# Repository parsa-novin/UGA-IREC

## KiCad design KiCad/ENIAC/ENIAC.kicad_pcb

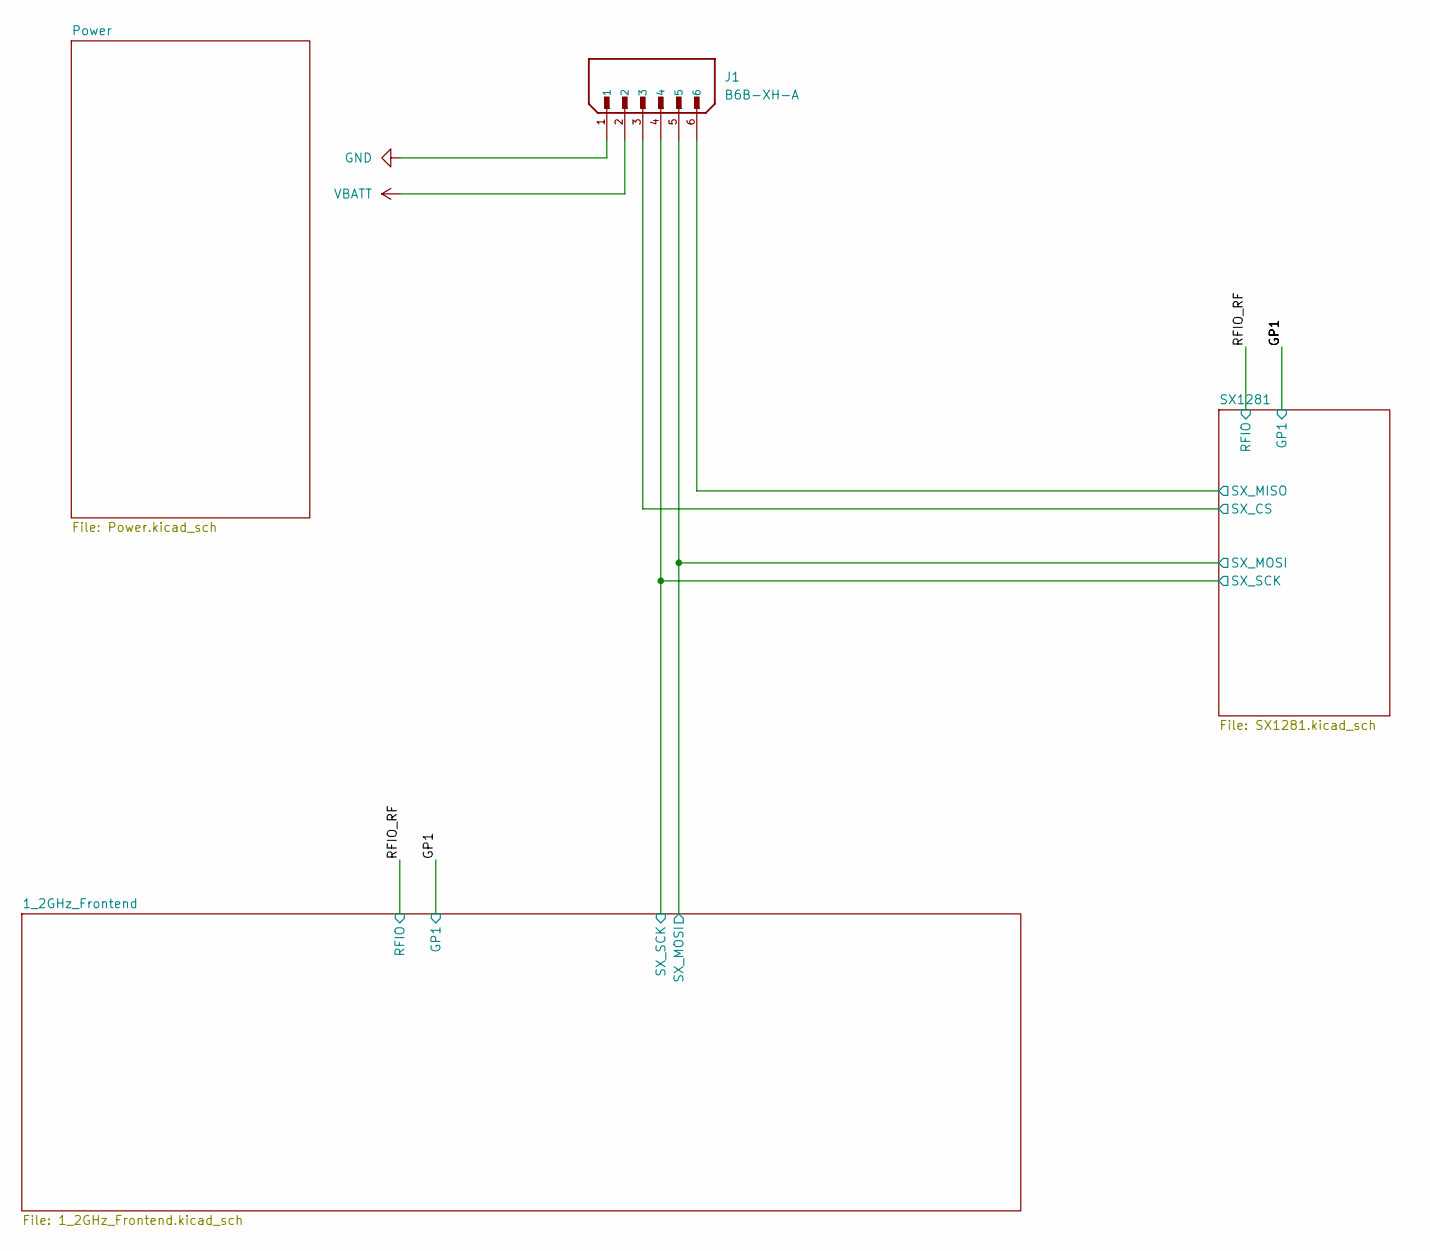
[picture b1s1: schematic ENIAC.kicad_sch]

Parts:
J1: B6B-XH-A; JST_EH_S6B-EH_1x06_P2.50mm_Horizontal; PARTREV 7/4/21

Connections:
/1_2GHz_Frontend/SX_MOSI: J1.5; also elsewhere on the board
/1_2GHz_Frontend/SX_SCK: J1.4; also elsewhere on the board
/SX1281/SX_CS: J1.3; also elsewhere on the board
/SX1281/SX_MISO: J1.6; also elsewhere on the board
VBATT: J1.2; also elsewhere on the board

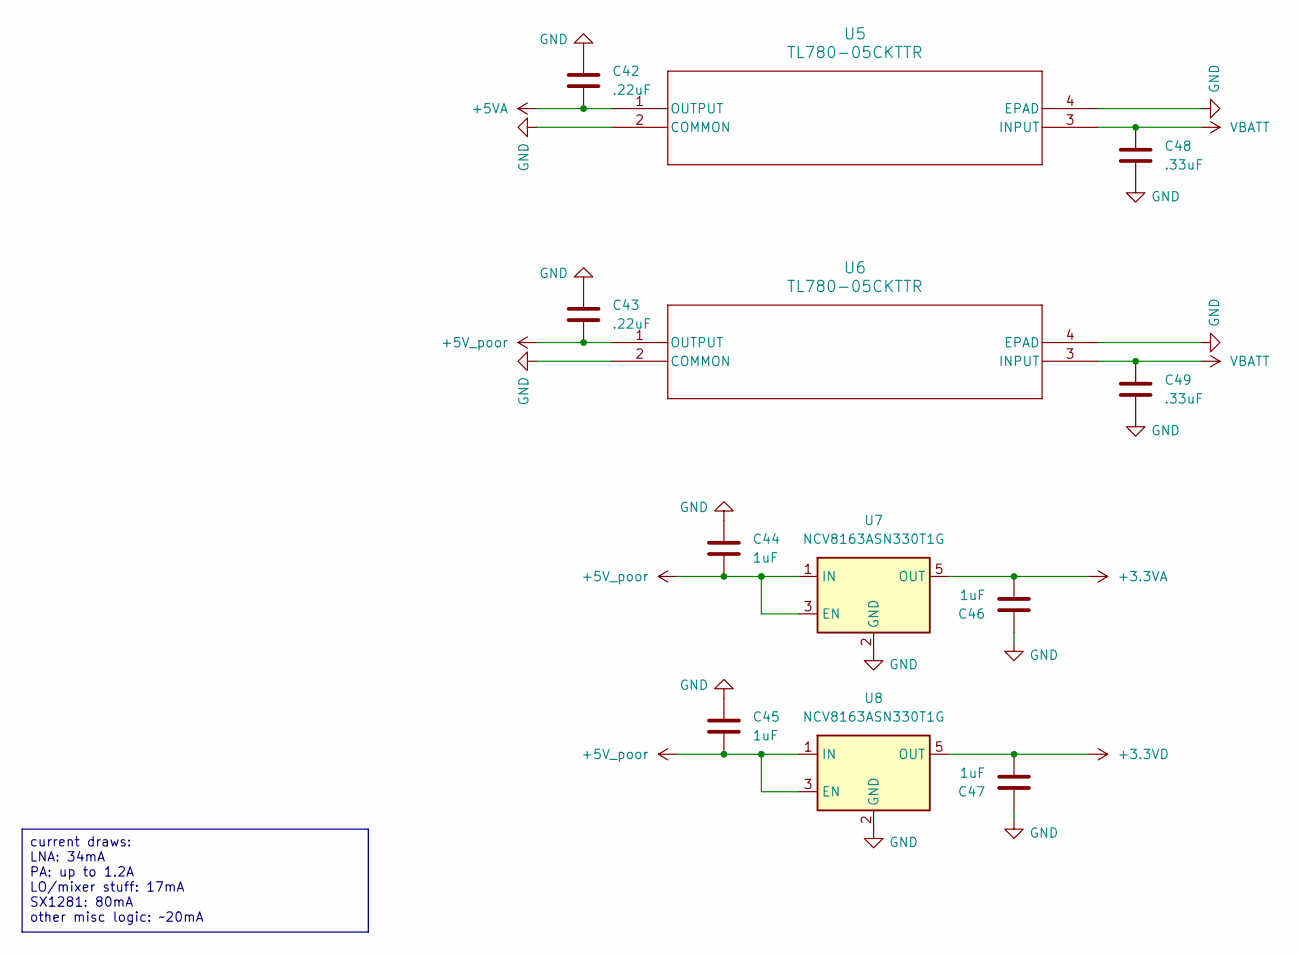
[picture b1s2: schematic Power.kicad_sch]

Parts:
C42, C43: .22uF; C_0603_1608Metric
C44, C45, C46, C47: 1uF; C_0603_1608Metric
C48, C49: .33uF; C_0603_1608Metric
U5, U6: TL780-05CKTTR; TO-263-3_TabPin4
U7, U8: NCV8163ASN330T1G; TSOT-23-5

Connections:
+3.3VA: C46.2, U7.5 (OUT); also elsewhere on the board
+3.3VD: C47.2, U8.5 (OUT); also elsewhere on the board
+5VA: C42.2, U5.1 (OUTPUT); also elsewhere on the board
+5V_poor: C43.2, C44.2, C45.2, U6.1 (OUTPUT), U7.1 (IN), U7.3 (EN), U8.1 (IN), U8.3 (EN)
VBATT: C48.1, C49.1, U5.3 (INPUT), U6.3 (INPUT); also elsewhere on the board

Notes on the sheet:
current draws: LNA: 34mA PA: up to 1.2A LO/mixer stuff: 17mA SX1281: 80mA other misc logic: ~20mA

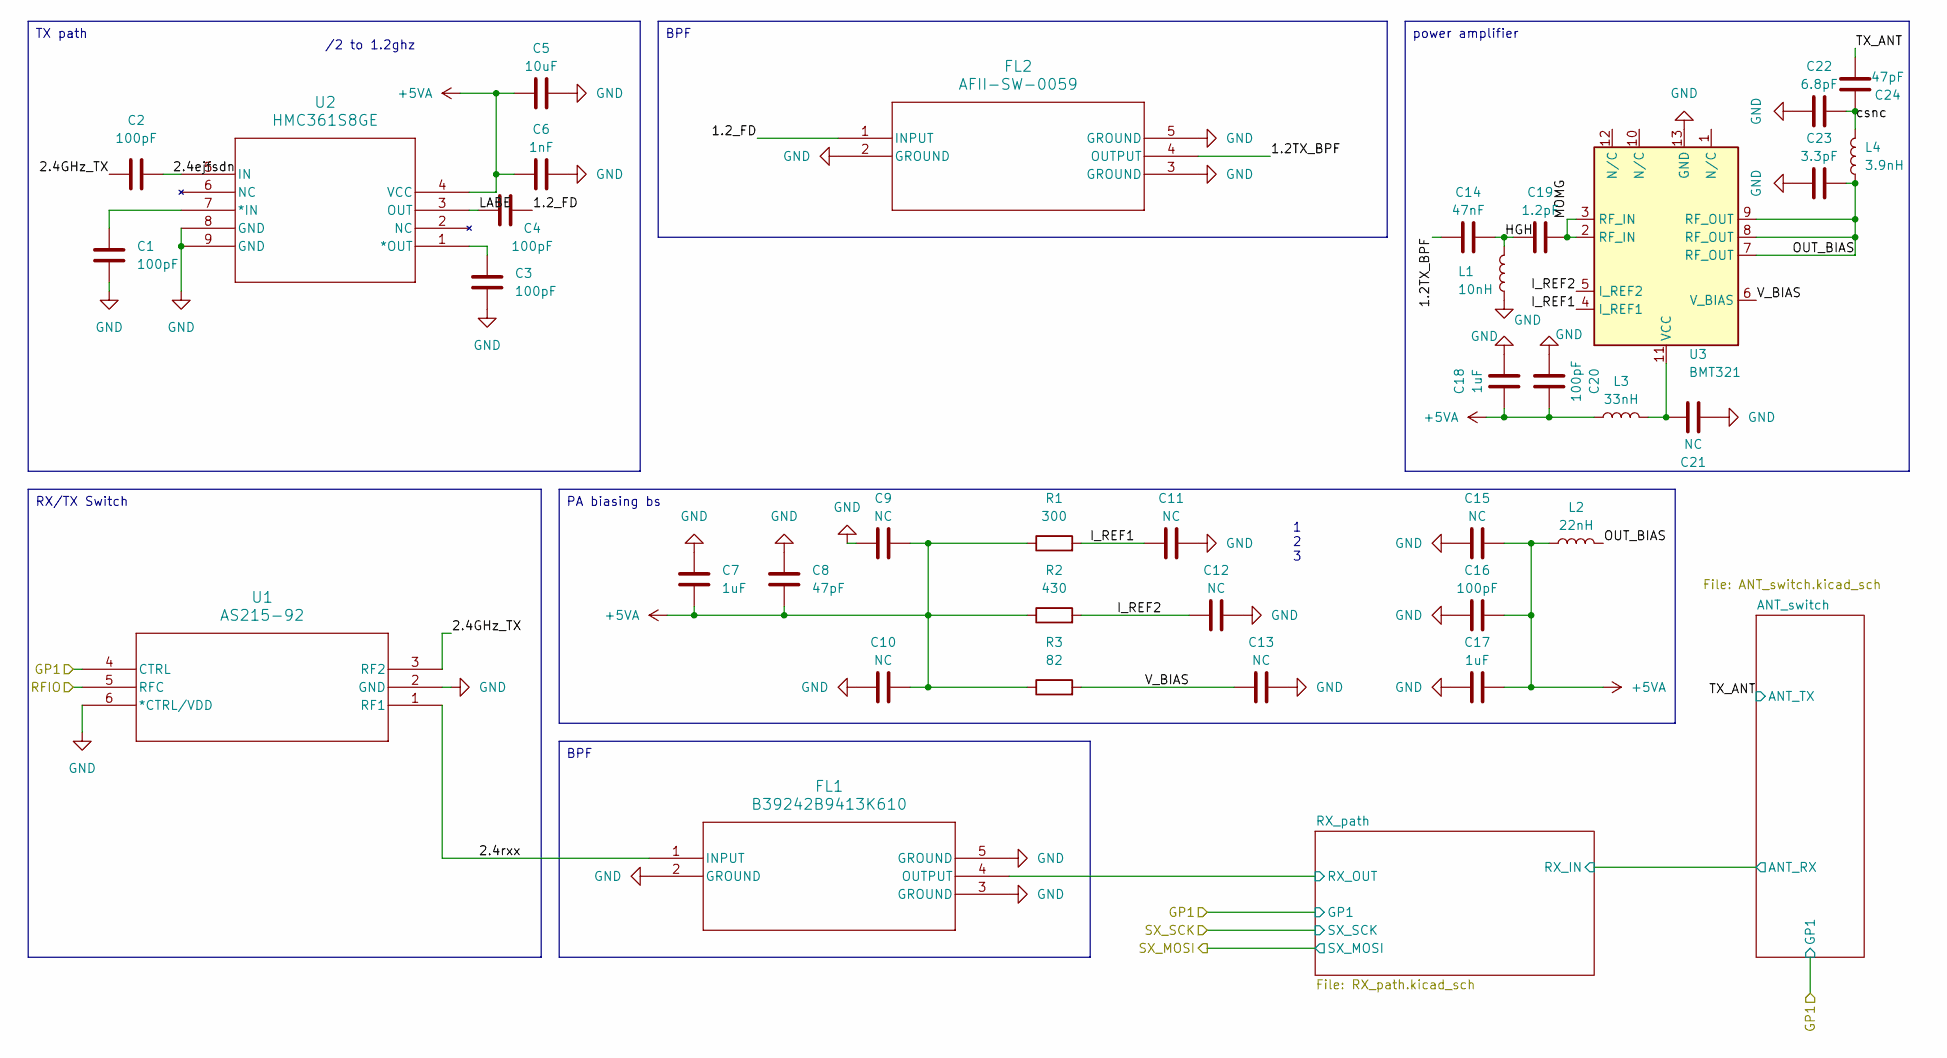
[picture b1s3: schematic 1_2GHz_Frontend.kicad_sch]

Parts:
C1, C2, C3, C4, C16, C20: 100pF; C_0603_1608Metric
C5: 10uF; C_0603_1608Metric
C6: 1nF; C_0603_1608Metric
C7, C17, C18: 1uF; C_0603_1608Metric
C8, C24: 47pF; C_0603_1608Metric
C9, C10, C11, C12, C13, C15, C21: NC; C_0603_1608Metric
C14: 47nF; C_0603_1608Metric
C19: 1.2pF; C_0603_1608Metric
C22: 6.8pF; C_0603_1608Metric
C23: 3.3pF; C_0603_1608Metric
FL1: B39242B9413K610; FIL_AFS14A04-1575.42-T3
FL2: AFII-SW-0059; FIL_AFS14A04-1575.42-T3
L1: 10nH; L_0603_1608Metric
L2: 22nH; L_0603_1608Metric
L3: 33nH; L_0603_1608Metric
L4: 3.9nH; L_0603_1608Metric
R1: 300; R_0603_1608Metric
R2: 430; R_0603_1608Metric
R3: 82; R_0603_1608Metric
U1: AS215-92; SOT-363_SC-70-6_Handsoldering
U2: HMC361S8GE; SOIC-8-1EP_3.9x4.9mm_P1.27mm_EP2.41x3.3mm_ThermalVias
U3: BMT321; VQFN-12-1EP_4x4mm_P0.8mm_EP2.1x2.1mm_ThermalVias

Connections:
+5VA: C5.1, C6.1, C7.2, C8.2, C9.1, C10.2, C15.2, C16.2, C17.2, C18.1, C20.2, L2.1, L3.1, R1.1, R2.1, R3.1, U2.4 (VCC); also elsewhere on the board
/1_2GHz_Frontend/1.2TX_BPF: C14.1, FL2.4 (OUTPUT)
/1_2GHz_Frontend/1.2_FD: C4.1, FL2.1 (INPUT)
/1_2GHz_Frontend/2.4GHz_TX: C2.1, U1.3 (RF2)
/1_2GHz_Frontend/2.4ejfsdn: C2.2, U2.5 (IN)
/1_2GHz_Frontend/2.4rxx: FL1.1 (INPUT), U1.1 (RF1)
/1_2GHz_Frontend/HGH: C14.2, C19.1, L1.2
/1_2GHz_Frontend/I_REF1: C11.1, R1.2, U3.4 (I_REF1)
/1_2GHz_Frontend/I_REF2: C12.1, R2.2, U3.5 (I_REF2)
/1_2GHz_Frontend/LABE: C4.2, U2.3 (OUT)
/1_2GHz_Frontend/MOMG: C19.2, U3.2 (RF_IN), U3.3 (RF_IN)
/1_2GHz_Frontend/OUT_BIAS: C23.2, L2.2, L4.1, U3.7 (RF_OUT), U3.8 (RF_OUT), U3.9 (RF_OUT)
/1_2GHz_Frontend/RX_path/RX_OUT: FL1.4 (OUTPUT); also elsewhere on the board
/1_2GHz_Frontend/TX_ANT: C24.2; also elsewhere on the board
/1_2GHz_Frontend/V_BIAS: C13.1, R3.2, U3.6 (V_BIAS)
/1_2GHz_Frontend/csnc: C22.2, C24.1, L4.2
/GP1: U1.4 (CTRL); also elsewhere on the board
/RFIO_RF: U1.5 (RFC); also elsewhere on the board
unnamed: C1.1, U2.7 (*IN)
unnamed: C3.1, U2.1 (*OUT)
unnamed: C21.2, L3.2, U3.11 (VCC)

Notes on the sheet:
1 2 3
/2 to 1.2ghz
BPF
RX/TX Switch
TX path
power amplifier
PA biasing bs

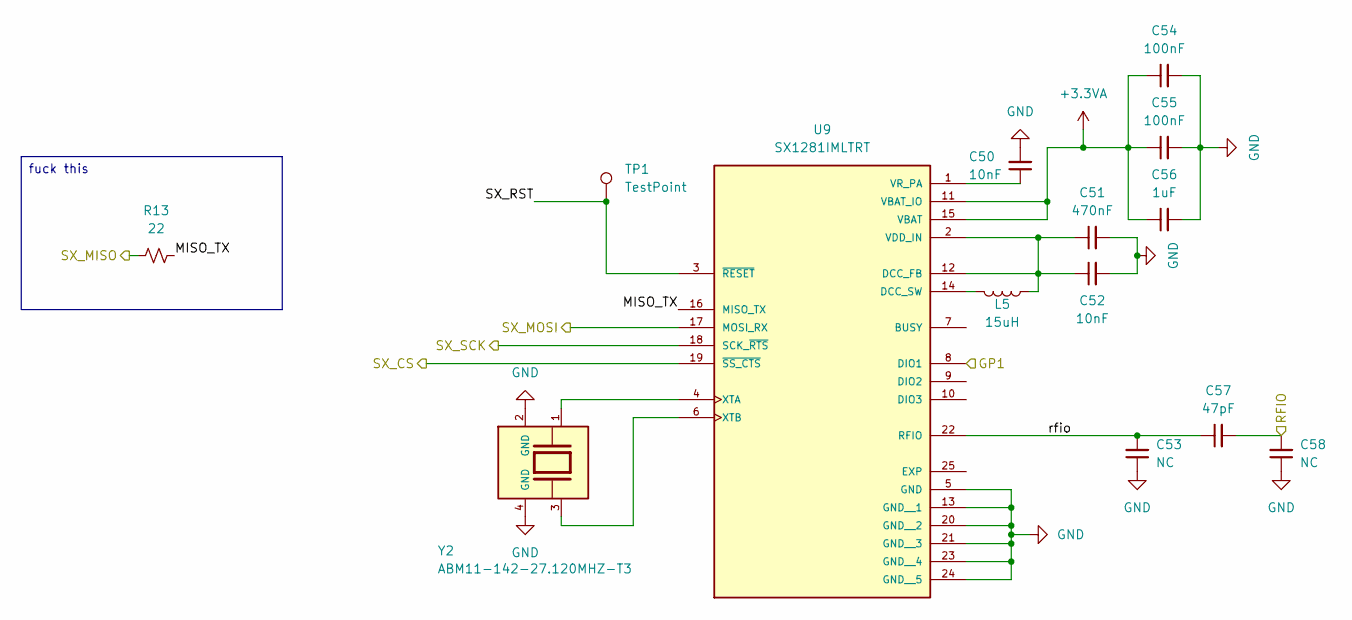
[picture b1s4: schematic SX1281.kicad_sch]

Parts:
C50, C52: 10nF; C_0603_1608Metric
C51: 470nF; C_0603_1608Metric
C53, C58: NC; C_0603_1608Metric
C54, C55: 100nF; C_0603_1608Metric
C56: 1uF; C_0603_1608Metric
C57: 47pF; C_0603_1608Metric
L5: 15uH; L_0603_1608Metric
R13: 22; R_0603_1608Metric
TP1: TestPoint
U9: SX1281IMLTRT; QFN-24-1EP_4x4mm_P0.5mm_EP2.6x2.6mm_ThermalVias; PARTREV 3.3
Y2: ABM11-142-27.120MHZ-T3; XTAL_ABM11-142-27.120MHZ-T3; PARTREV 06.19.15

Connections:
+3.3VA: C54.1, C55.1, C56.1, U9.11 (VBAT_IO), U9.15 (VBAT); also elsewhere on the board
/1_2GHz_Frontend/SX_MOSI: U9.17 (MOSI_RX); also elsewhere on the board
/1_2GHz_Frontend/SX_SCK: U9.18 (SCK_~RTS); also elsewhere on the board
/GP1: U9.8 (DIO1); also elsewhere on the board
/RFIO_RF: C57.2, C58.2; also elsewhere on the board
/SX1281/MISO_TX: R13.1, U9.16 (MISO_TX)
/SX1281/SX_CS: U9.19 (~SS_CTS); also elsewhere on the board
/SX1281/SX_MISO: R13.2; also elsewhere on the board
/SX1281/SX_RST: TP1.1, U9.3 (~RESET)
/SX1281/rfio: C53.2, C57.1, U9.22 (RFIO)
unnamed: C51.1, C52.1, L5.1, U9.2 (VDD_IN), U9.12 (DCC_FB)
unnamed: L5.2, U9.14 (DCC_SW)
unnamed: C50.1, U9.1 (VR_PA)
unnamed: U9.4 (XTA), Y2.1
unnamed: U9.6 (XTB), Y2.3

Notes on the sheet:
fuck this

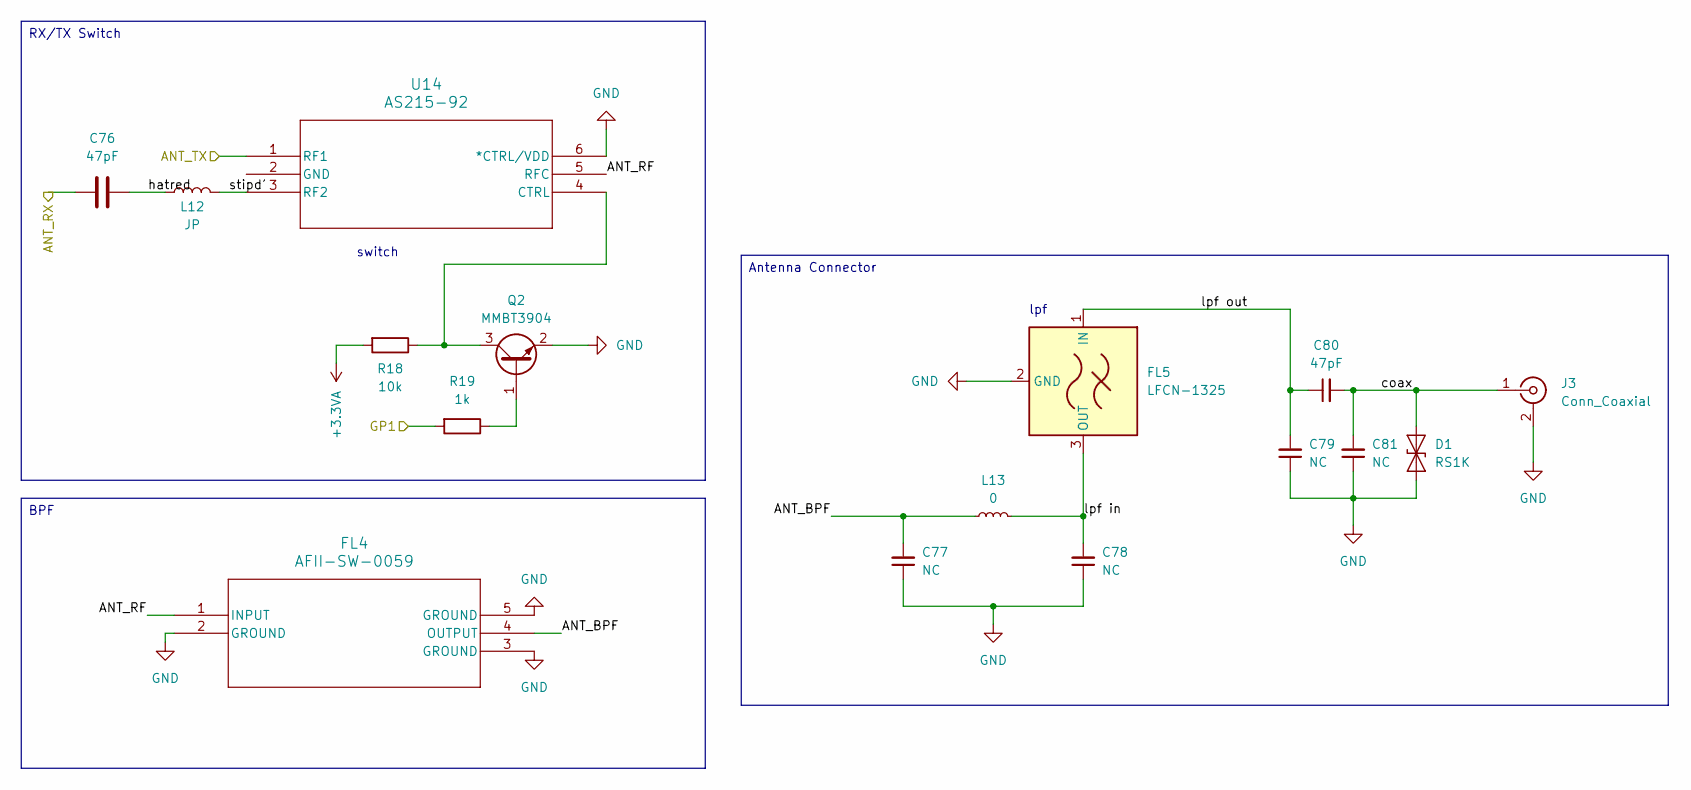
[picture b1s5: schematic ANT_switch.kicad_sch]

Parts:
C76, C80: 47pF; C_0603_1608Metric
C77, C78, C79, C81: NC; C_0603_1608Metric
D1: RS1K; D_SMA
FL4: AFII-SW-0059; FIL_AFS14A04-1575.42-T3
FL5: LFCN-1325; Filter_Mini-Circuits_FV1206
J3: Conn_Coaxial; SMA_Molex_73251-1153_EdgeMount_Horizontal
L12: JP; L_0603_1608Metric
L13: 0; L_0603_1608Metric
Q2: MMBT3904; SOT-23
R18: 10k; R_0603_1608Metric
R19: 1k; R_0603_1608Metric
U14: AS215-92; SOT-363_SC-70-6_Handsoldering

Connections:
+3.3VA: R18.2; also elsewhere on the board
/1_2GHz_Frontend/ANT_switch/ANT_BPF: C77.2, FL4.4 (OUTPUT), L13.1
/1_2GHz_Frontend/ANT_switch/ANT_RF: FL4.1 (INPUT), U14.5 (RFC)
/1_2GHz_Frontend/ANT_switch/ANT_RX: C76.1; also elsewhere on the board
/1_2GHz_Frontend/ANT_switch/coax: C80.2, C81.2, D1.2 (A2), J3.1 (In)
/1_2GHz_Frontend/ANT_switch/hatred: C76.2, L12.1
/1_2GHz_Frontend/ANT_switch/lpf in: C78.2, FL5.3 (OUT), L13.2
/1_2GHz_Frontend/ANT_switch/lpf out: C79.2, C80.1, FL5.1 (IN)
/1_2GHz_Frontend/ANT_switch/stipd': L12.2, U14.3 (RF2)
/1_2GHz_Frontend/TX_ANT: U14.1 (RF1); also elsewhere on the board
/GP1: R19.2; also elsewhere on the board
unnamed: Q2.1 (B), R19.1
unnamed: Q2.3 (C), R18.1, U14.4 (CTRL)

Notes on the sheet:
switch
lpf
Antenna Connector
RX/TX Switch
BPF

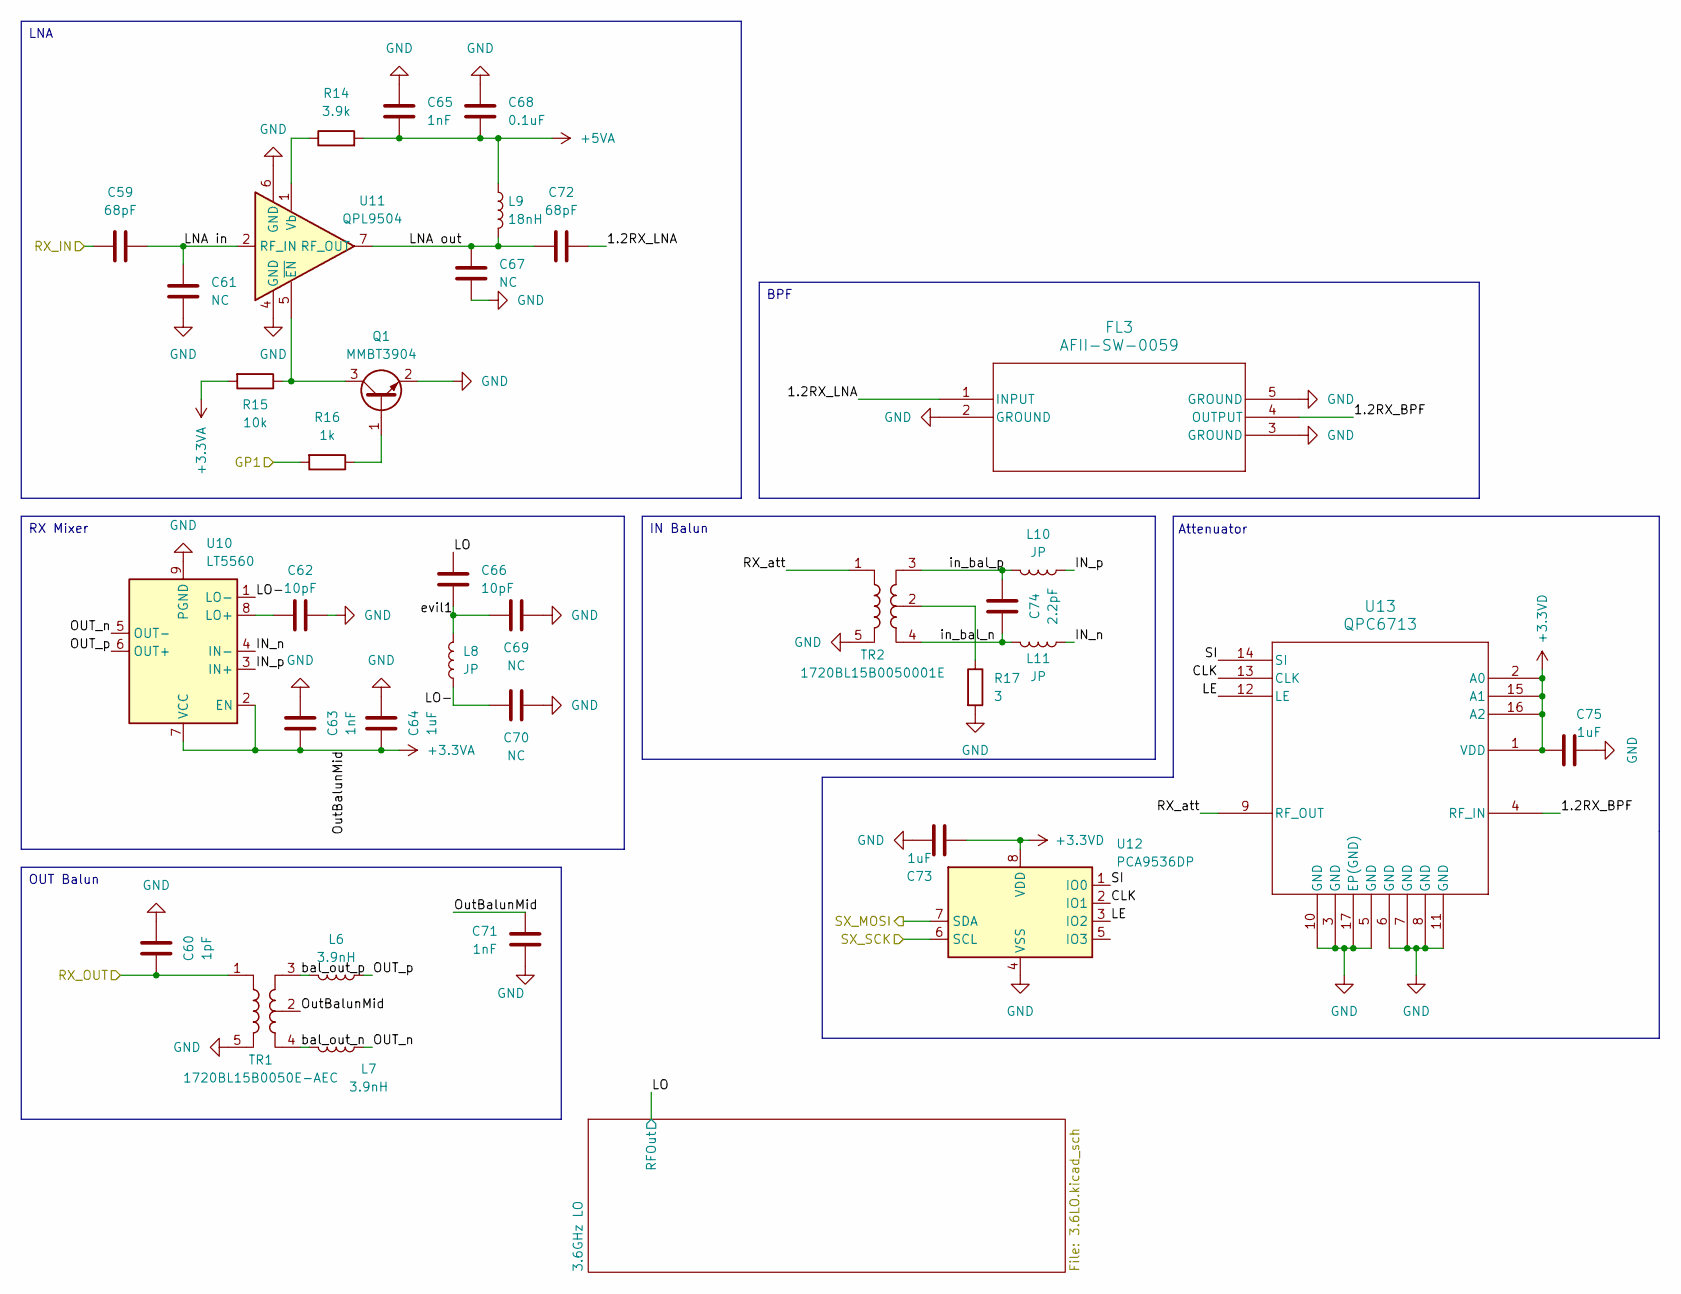
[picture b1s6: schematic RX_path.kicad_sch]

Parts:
C59, C72: 68pF; C_0603_1608Metric
C60: 1pF; C_0603_1608Metric
C61, C67, C69, C70: NC; C_0603_1608Metric
C62, C66: 10pF; C_0603_1608Metric
C63, C65, C71: 1nF; C_0603_1608Metric
C64, C73, C75: 1uF; C_0603_1608Metric
C68: 0.1uF; C_0603_1608Metric
C74: 2.2pF; C_0603_1608Metric
FL3: AFII-SW-0059; FIL_AFS14A04-1575.42-T3
L6, L7: 3.9nH; L_0603_1608Metric
L8, L10, L11: JP; L_0603_1608Metric
L9: 18nH; L_0603_1608Metric
Q1: MMBT3904; SOT-23
R14: 3.9k; R_0603_1608Metric
R15: 10k; R_0603_1608Metric
R16: 1k; R_0603_1608Metric
R17: 3; R_0603_1608Metric
TR1: 1720BL15B0050E-AEC; SMT_15B0050E_JOT
TR2: 1720BL15B0050001E; SMT_15B0050E_JOT
U10: LT5560; DFN-8-1EP_3x3mm_P0.5mm_EP1.66x2.38mm
U11: QPL9504; DFN-8-1EP_2x2mm_P0.5mm_EP0.8x1.6mm
U12: PCA9536DP; TSSOP-8_3x3mm_P0.65mm
U13: QPC6713; QFN-16-1EP_3x3mm_P0.5mm_EP1.7x1.7mm_ThermalVias

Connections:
+3.3VA: C63.1, C64.1, C71.1, R15.2, TR1.2, U10.2 (EN), U10.7 (VCC); also elsewhere on the board
+3.3VD: C73.1, C75.1, U12.8 (VDD), U13.1 (VDD), U13.2 (A0), U13.15 (A1), U13.16 (A2); also elsewhere on the board
+5VA: C65.2, C68.2, L9.1, R14.2; also elsewhere on the board
/1_2GHz_Frontend/ANT_switch/ANT_RX: C59.1; also elsewhere on the board
/1_2GHz_Frontend/RX_path/1.2RX_BPF: FL3.4 (OUTPUT), U13.4 (RF_IN)
/1_2GHz_Frontend/RX_path/1.2RX_LNA: C72.2, FL3.1 (INPUT)
/1_2GHz_Frontend/RX_path/CLK: U12.2 (IO1), U13.13 (CLK)
/1_2GHz_Frontend/RX_path/IN_n: L11.1, U10.4 (IN-)
/1_2GHz_Frontend/RX_path/IN_p: L10.1, U10.3 (IN+)
/1_2GHz_Frontend/RX_path/LE: U12.3 (IO2), U13.12 (LE)
/1_2GHz_Frontend/RX_path/LNA in: C59.2, C61.1, U11.2 (RF_IN)
/1_2GHz_Frontend/RX_path/LNA out: C67.1, C72.1, L9.2, U11.7 (RF_OUT)
/1_2GHz_Frontend/RX_path/LO: C66.1; also elsewhere on the board
/1_2GHz_Frontend/RX_path/LO-: C70.1, L8.1, U10.1 (LO-)
/1_2GHz_Frontend/RX_path/OUT_n: L7.1, U10.5 (OUT-)
/1_2GHz_Frontend/RX_path/OUT_p: L6.1, U10.6 (OUT+)
/1_2GHz_Frontend/RX_path/RX_OUT: C60.1, TR1.1; also elsewhere on the board
/1_2GHz_Frontend/RX_path/RX_att: TR2.1, U13.9 (RF_OUT)
/1_2GHz_Frontend/RX_path/SI: U12.1 (IO0), U13.14 (SI)
/1_2GHz_Frontend/RX_path/bal_out_n: L7.2, TR1.4
/1_2GHz_Frontend/RX_path/bal_out_p: L6.2, TR1.3
/1_2GHz_Frontend/RX_path/evil1: C66.2, C69.1, L8.2
/1_2GHz_Frontend/RX_path/in_bal_n: C74.1, L11.2, TR2.4
/1_2GHz_Frontend/RX_path/in_bal_p: C74.2, L10.2, TR2.3
/1_2GHz_Frontend/SX_MOSI: U12.7 (SDA); also elsewhere on the board
/1_2GHz_Frontend/SX_SCK: U12.6 (SCL); also elsewhere on the board
/GP1: R16.2; also elsewhere on the board
unnamed: Q1.1 (B), R16.1
unnamed: R17.1, TR2.2
unnamed: C62.1, U10.8 (LO+)
unnamed: R14.1, U11.1 (Vb)

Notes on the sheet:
Attenuator
LNA
OUT Balun
IN Balun
RX Mixer
BPF

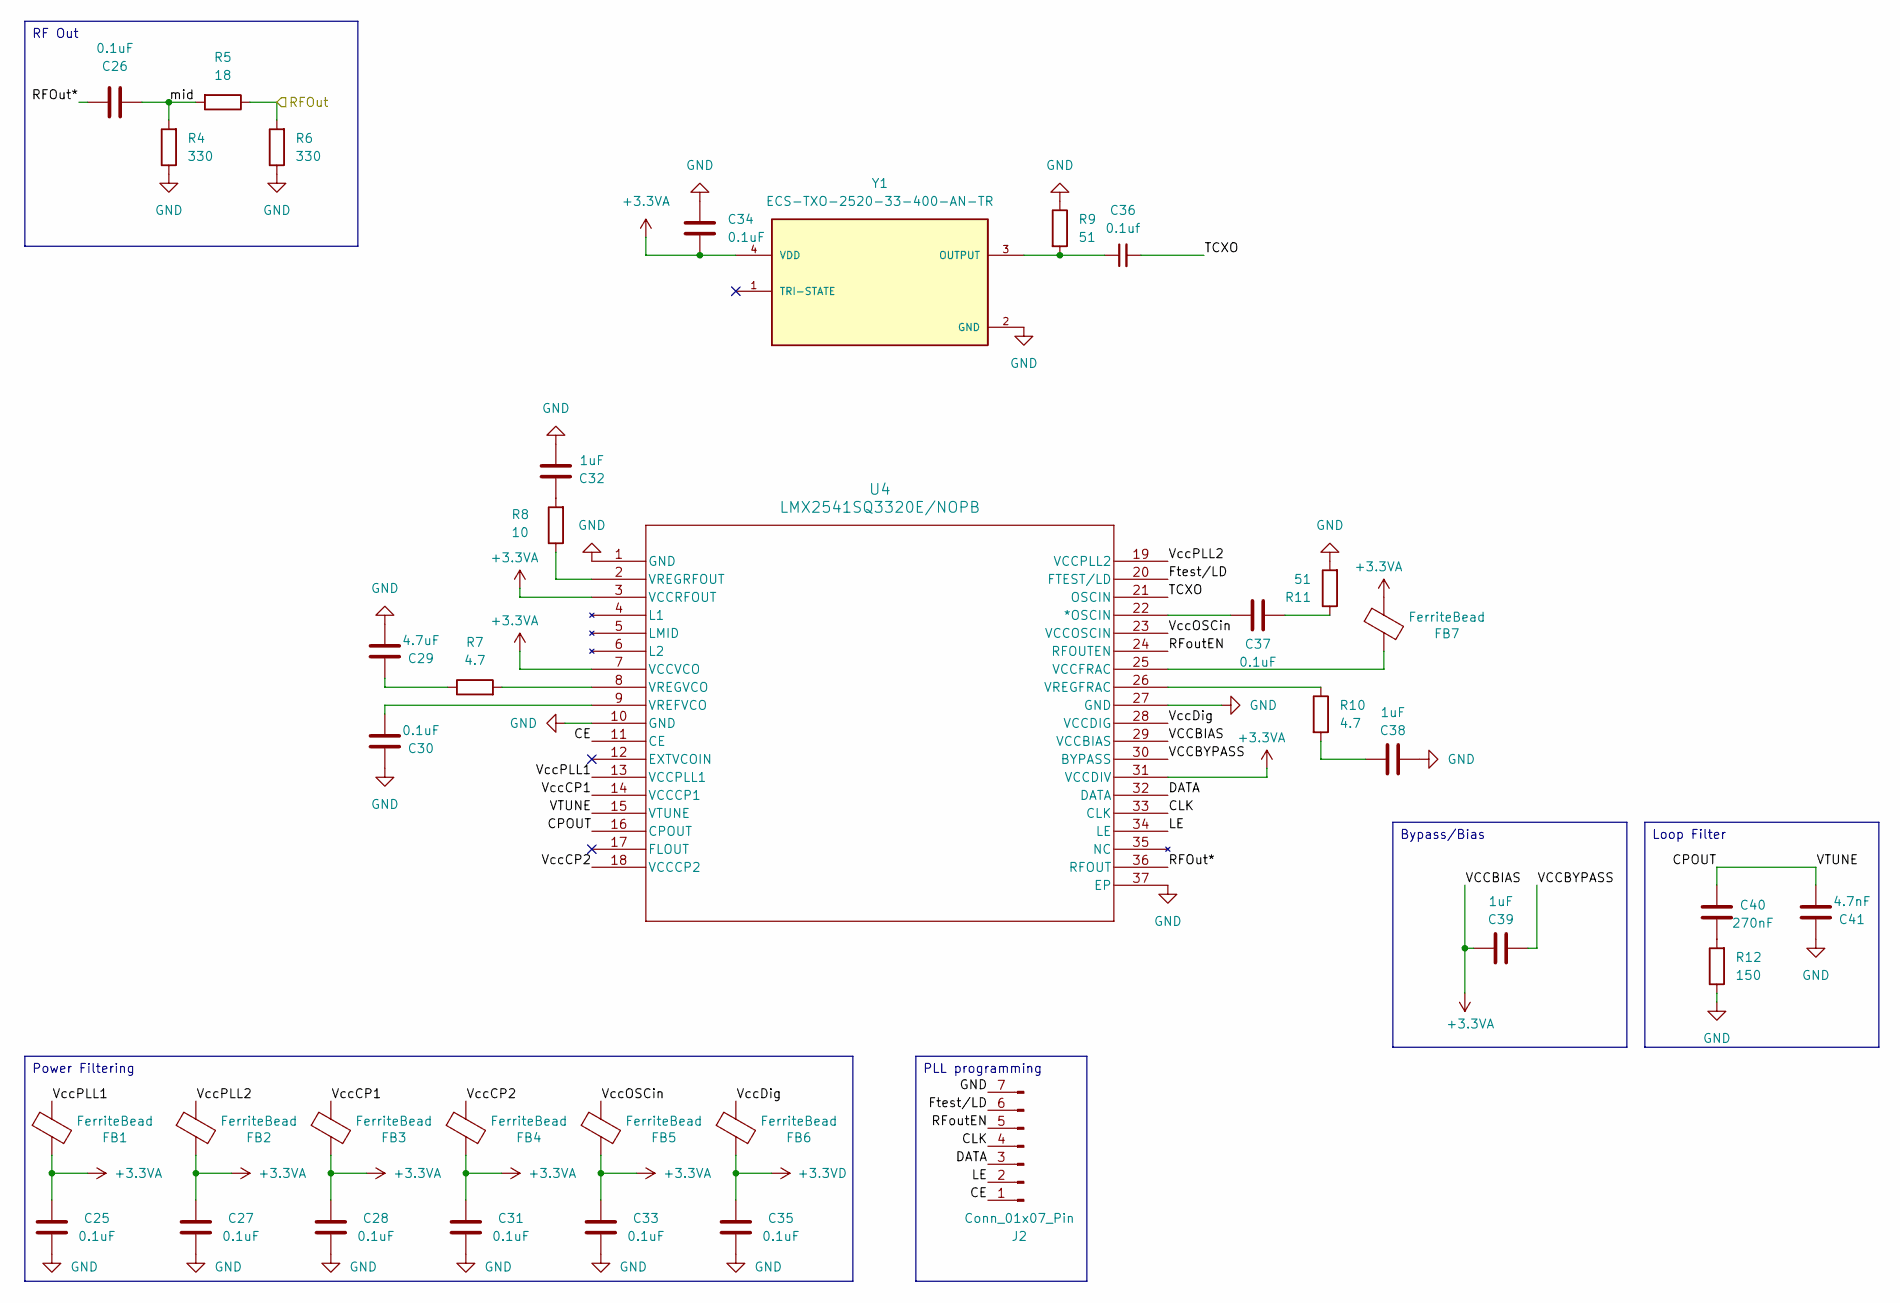
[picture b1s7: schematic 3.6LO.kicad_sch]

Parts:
C25, C26, C27, C28, C30, C31, C33, C34, C35, C37: 0.1uF; C_0603_1608Metric
C29: 4.7uF; C_0603_1608Metric
C32, C38, C39: 1uF; C_0603_1608Metric
C36: 0.1uf; C_0603_1608Metric
C40: 270nF; C_0603_1608Metric
C41: 4.7nF; C_0603_1608Metric
FB1, FB2, FB3, FB4, FB5, FB6, FB7: FerriteBead; L_0402_1005Metric_Pad0.77x0.64mm_HandSolder
J2: Conn_01x07_Pin; PinHeader_1x07_P2.54mm_Vertical
R4, R6: 330; R_0603_1608Metric
R5: 18; R_0603_1608Metric
R7, R10: 4.7; R_0603_1608Metric
R8: 10; R_0603_1608Metric
R9, R11: 51; R_0603_1608Metric
R12: 150; R_0603_1608Metric
U4: LMX2541SQ3320E/NOPB; SQA36A
Y1: ECS-TXO-2520-33-400-AN-TR; OSC_ECS-TXO-2520-33-400-AN-TR; PARTREV 2017

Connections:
+3.3VA: C25.2, C27.2, C28.2, C31.2, C33.2, C34.2, C39.1, FB1.2, FB2.2, FB3.2, FB4.2, FB5.2, FB7.1, U4.3 (VCCRFOUT), U4.7 (VCCVCO), U4.29 (VCCBIAS), U4.31 (VCCDIV), Y1.4 (VDD); also elsewhere on the board
+3.3VD: C35.2, FB6.2; also elsewhere on the board
/1_2GHz_Frontend/RX_path/3.6GHz LO/CE: J2.1, U4.11 (CE)
/1_2GHz_Frontend/RX_path/3.6GHz LO/CLK: J2.4, U4.33 (CLK)
/1_2GHz_Frontend/RX_path/3.6GHz LO/CPOUT: C40.1, C41.1, U4.15 (VTUNE), U4.16 (CPOUT)
/1_2GHz_Frontend/RX_path/3.6GHz LO/DATA: J2.3, U4.32 (DATA)
/1_2GHz_Frontend/RX_path/3.6GHz LO/Ftest/LD: J2.6, U4.20 (FTEST/LD)
/1_2GHz_Frontend/RX_path/3.6GHz LO/LE: J2.2, U4.34 (LE)
/1_2GHz_Frontend/RX_path/3.6GHz LO/RFOut*: C26.2, U4.36 (RFOUT)
/1_2GHz_Frontend/RX_path/3.6GHz LO/RFoutEN: J2.5, U4.24 (RFOUTEN)
/1_2GHz_Frontend/RX_path/3.6GHz LO/TCXO: C36.2, U4.21 (OSCIN)
/1_2GHz_Frontend/RX_path/3.6GHz LO/VCCBYPASS: C39.2, U4.30 (BYPASS)
/1_2GHz_Frontend/RX_path/3.6GHz LO/VccCP1: FB3.1, U4.14 (VCCCP1)
/1_2GHz_Frontend/RX_path/3.6GHz LO/VccCP2: FB4.1, U4.18 (VCCCP2)
/1_2GHz_Frontend/RX_path/3.6GHz LO/VccDig: FB6.1, U4.28 (VCCDIG)
/1_2GHz_Frontend/RX_path/3.6GHz LO/VccOSCin: FB5.1, U4.23 (VCCOSCIN)
/1_2GHz_Frontend/RX_path/3.6GHz LO/VccPLL1: FB1.1, U4.13 (VCCPLL1)
/1_2GHz_Frontend/RX_path/3.6GHz LO/VccPLL2: FB2.1, U4.19 (VCCPLL2)
/1_2GHz_Frontend/RX_path/3.6GHz LO/mid: C26.1, R4.2, R5.2
/1_2GHz_Frontend/RX_path/LO: R5.1, R6.2; also elsewhere on the board
unnamed: C29.2, R7.1
unnamed: C32.2, R8.2
unnamed: C37.1, R11.1
unnamed: C38.1, R10.2
unnamed: C40.2, R12.2
unnamed: C37.2, U4.22 (*OSCIN)
unnamed: FB7.2, U4.25 (VCCFRAC)
unnamed: C30.1, U4.9 (VREFVCO)
unnamed: R10.1, U4.26 (VREGFRAC)
unnamed: R8.1, U4.2 (VREGRFOUT)
unnamed: R7.2, U4.8 (VREGVCO)
unnamed: C36.1, R9.2, Y1.3 (OUTPUT)

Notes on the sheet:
RF Out
Bypass/Bias
Power Filtering
Loop Filter
PLL programming

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
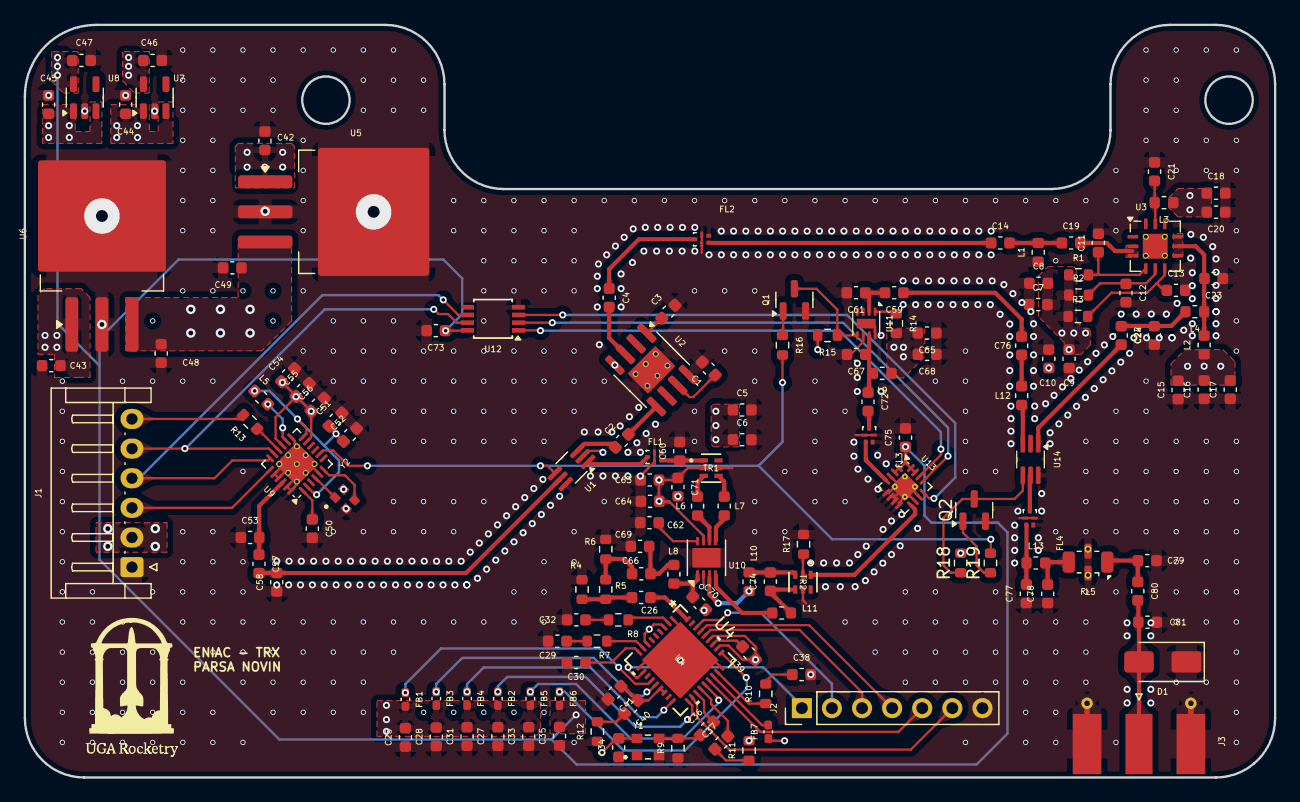
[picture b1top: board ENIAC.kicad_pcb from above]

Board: 4 copper layers, 105.5 x 63.5 mm, 149 parts (0 on the bottom side), 101 nets.

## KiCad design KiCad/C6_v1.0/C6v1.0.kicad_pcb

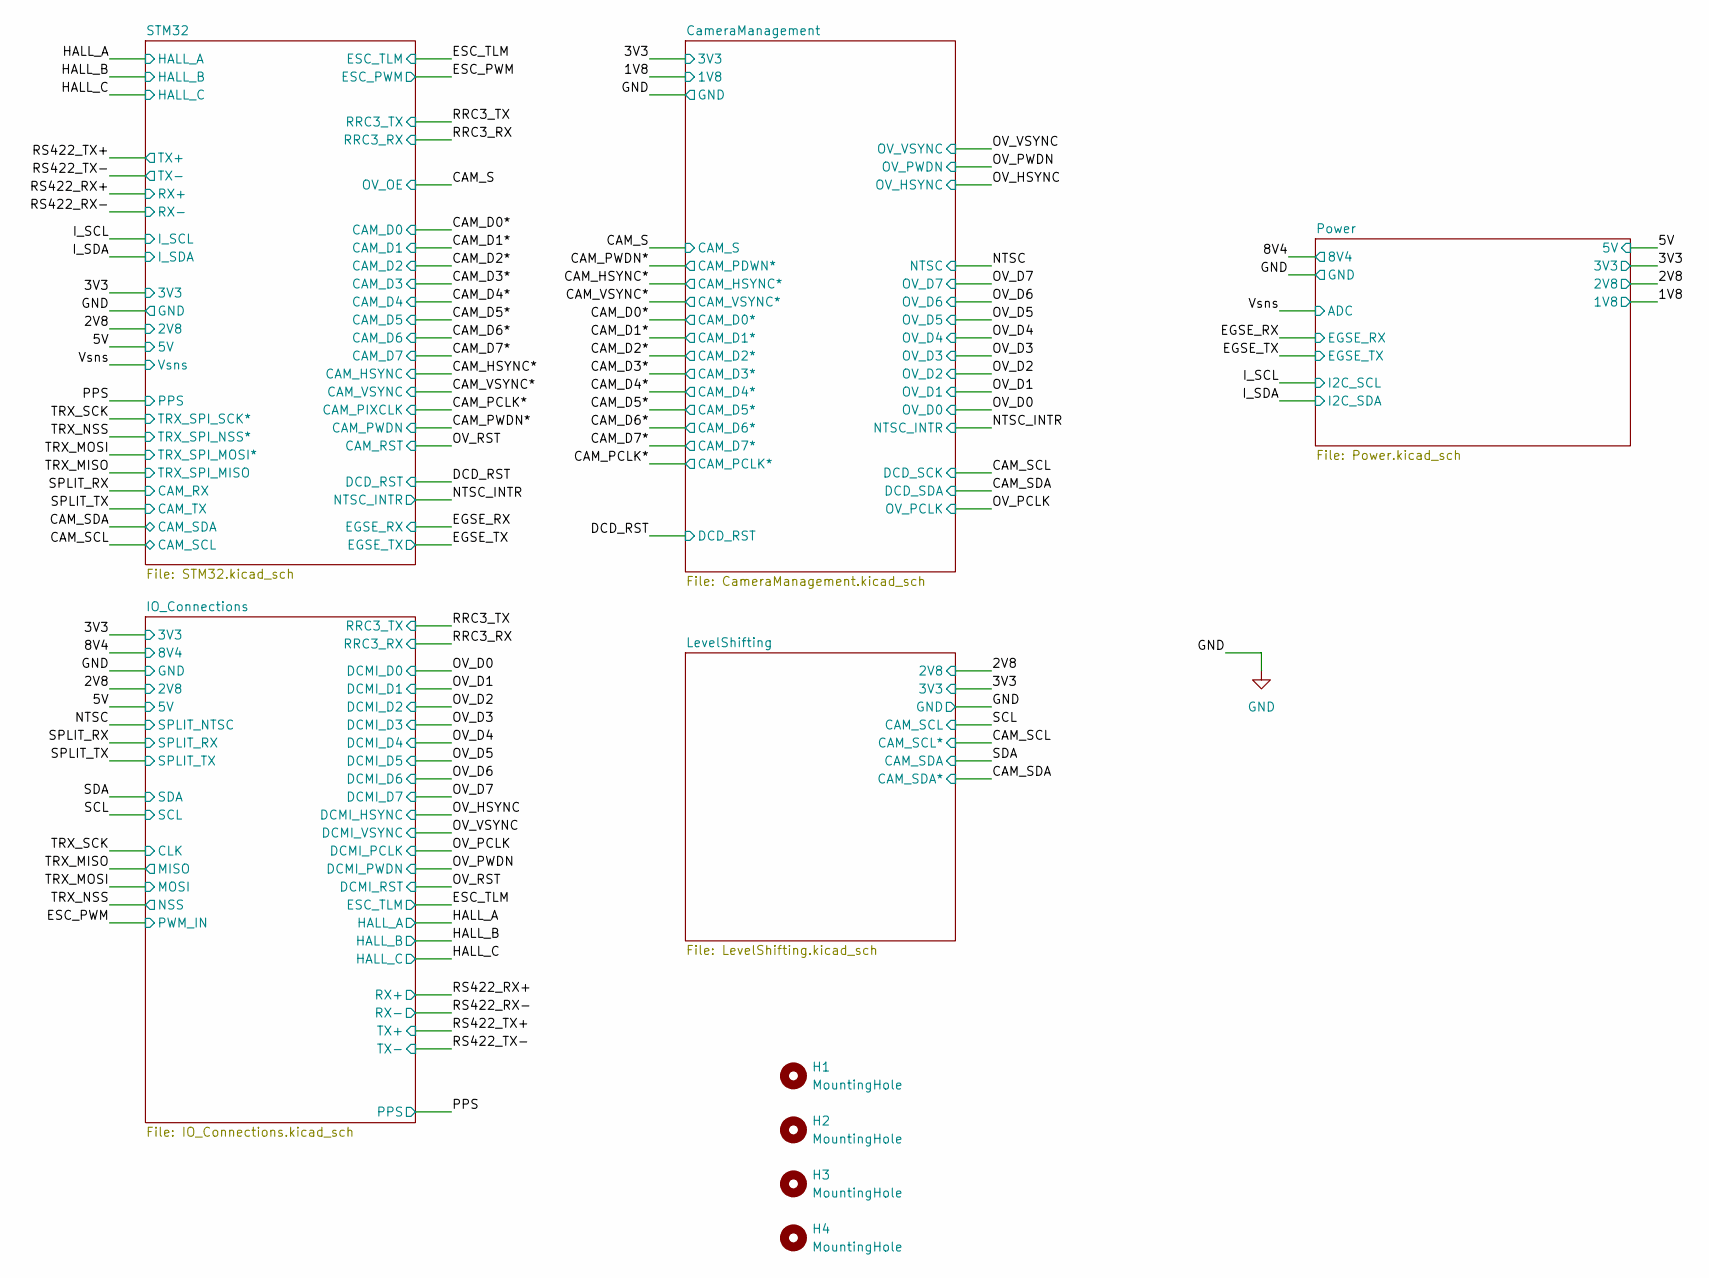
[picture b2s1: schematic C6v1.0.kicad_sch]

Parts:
H1, H2, H3, H4: MountingHole; MountingHole_2.2mm_M2_Pad

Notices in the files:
Embedded Programming/h7/Core/Src/main.c:
Copyright (c) 2026 STMicroelectronics.
All rights reserved.
This software is licensed under terms that can be found in the LICENSE file
KiCad/Satnogs_controller/satnogs_controller.kicad_pcb:
© Libre Space Foundation
